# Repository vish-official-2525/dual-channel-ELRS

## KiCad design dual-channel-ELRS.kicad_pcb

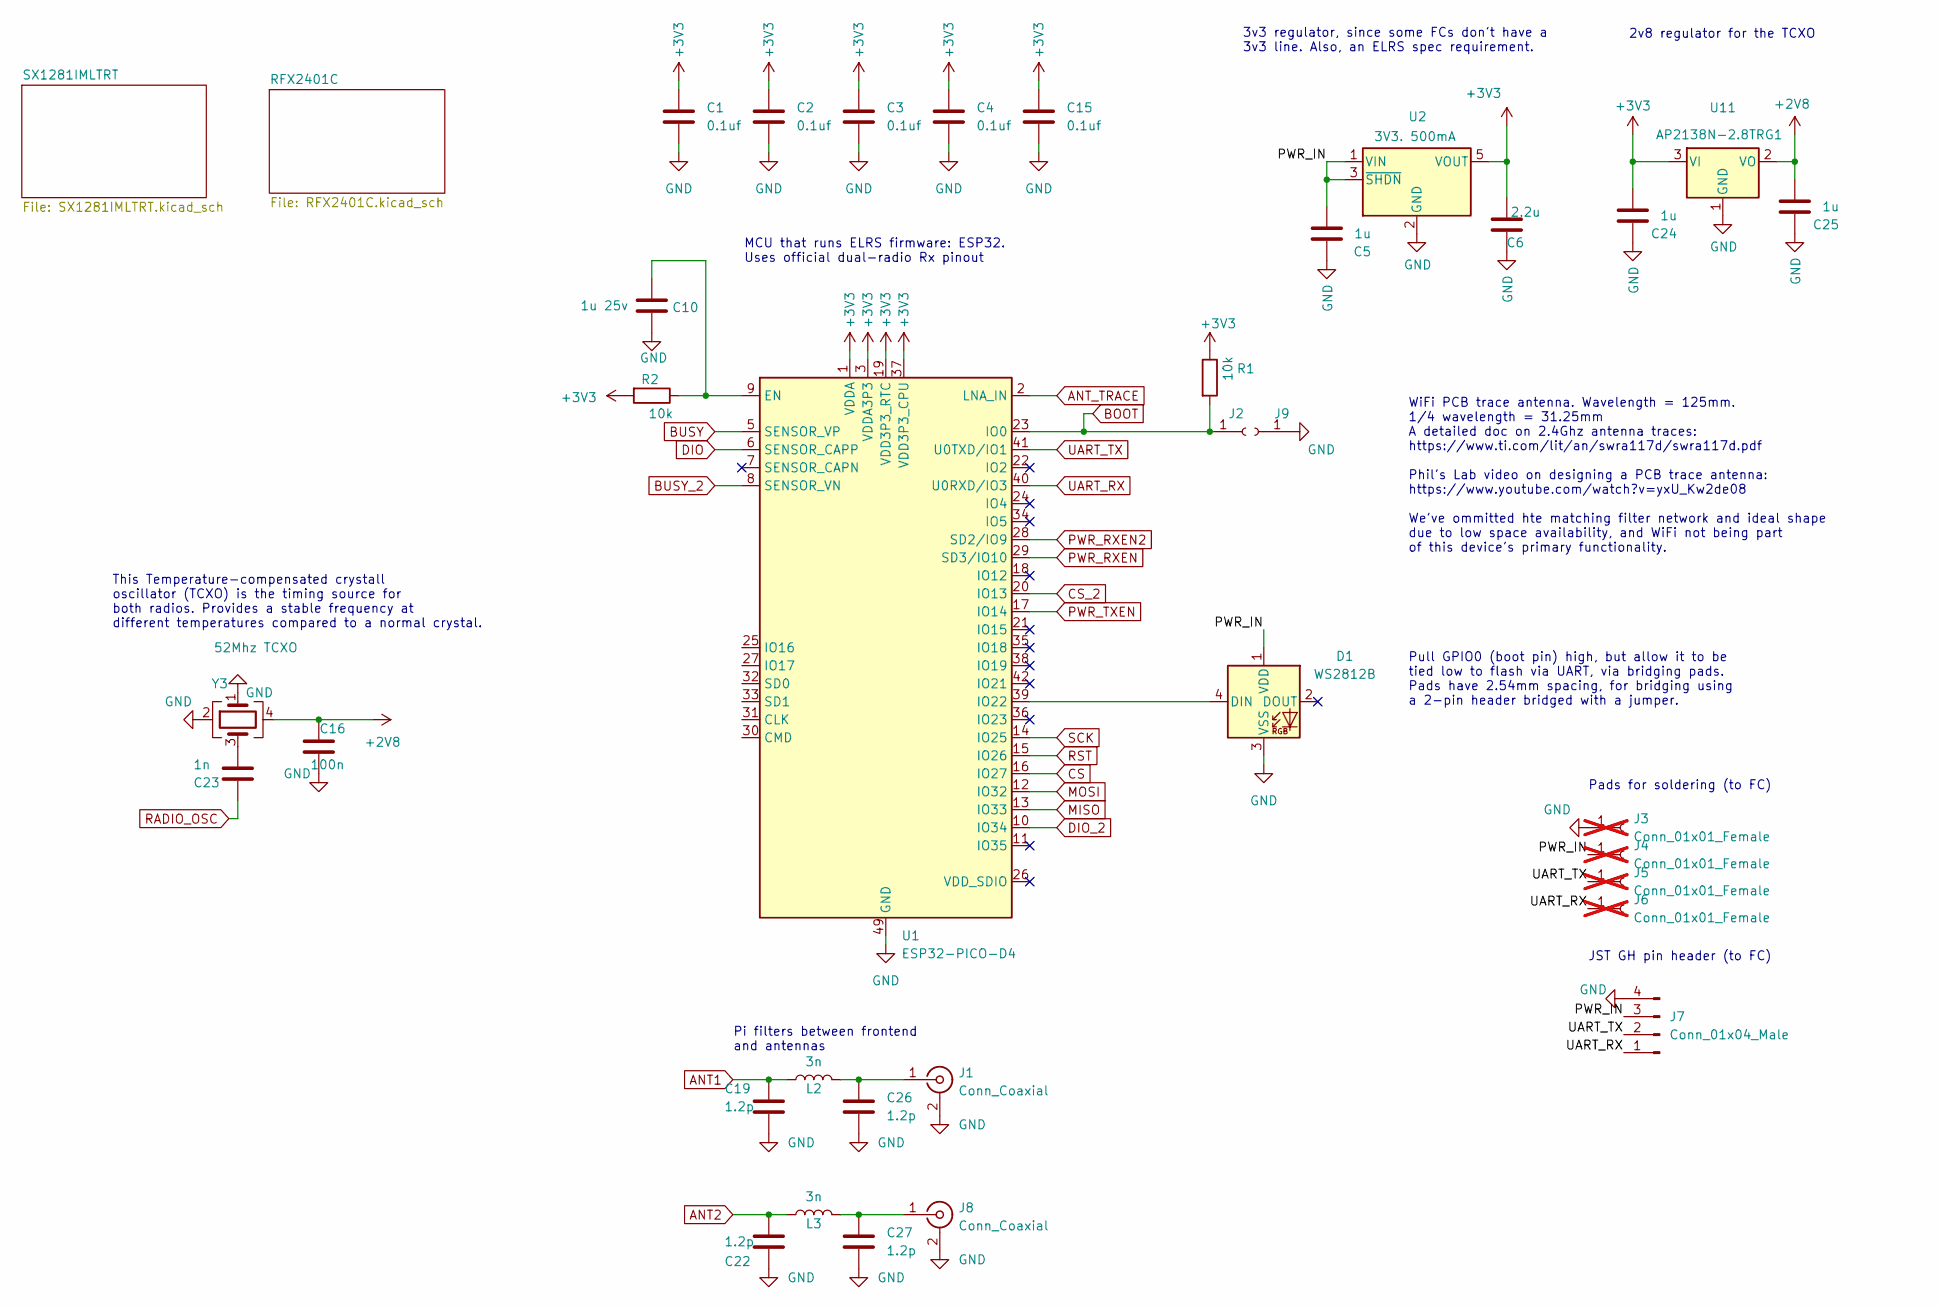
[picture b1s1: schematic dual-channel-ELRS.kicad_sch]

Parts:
C1, C2, C3, C4, C15: 0.1uf; C_0402_1005Metric
C5, C24, C25: 1u; C_0402_1005Metric; LCSC C52923
C6: 2.2u; C_0402_1005Metric; LCSC C12530
C10: 1u 25v; C_0402_1005Metric; LCSC C52923
C16: 100n; C_0402_1005Metric; LCSC C1525
C19, C22, C26, C27: 1.2p; C_0402_1005Metric; LCSC C327292
C23: 1n; C_0402_1005Metric; LCSC C1523
D1: WS2812B; LED_WS2812B_PLCC4_5.0x5.0mm_P3.2mm
J1, J8: Conn_Coaxial; U.FL_Hirose_U.FL-R-SMT-1_Vertical; Part Hirose U.FL-R-SMT-1(80); LCSC C88374
J2, J9: Conn_01x01_Female; TestPoint_Pad_1.0x1.0mm
J3, J4, J5, J6: Conn_01x01_Female; TestPoint_Pad_2.5x2.5mm; not fitted
J7: Conn_01x04_Male; JST_GH_SM04B-GHS-TB_1x04-1MP_P1.25mm_Horizontal; LCSC C189895
L2, L3: 3n; L_0402_1005Metric; LCSC C269824
R1, R2: 10k; R_0402_1005Metric; LCSC C25744
U1: ESP32-PICO-D4; QFN-48-1EP_7x7mm_P0.5mm_EP5.3x5.3mm
U2: 3V3. 500mA; TSOT-23-5; Part TPRT9013-33GB; LCSC C587158
U11: AP2138N-2.8TRG1; SOT-23; LCSC C176956
Y3: 52Mhz TCXO; Crystal_SMD_2016-4Pin_2.0x1.6mm; Digikey 2151-RTX-2016BD32-S-52.000-TR-NS1TR-ND

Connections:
BUSY_2: U1.8 (SENSOR_VN)
+2V8: C16.1, C25.2, U11.2 (VO), Y3.4
+3V3: C1.1, C2.1, C3.1, C4.1, C6.2, C15.1, C24.2, R1.1, R2.2, U1.1 (VDDA), U1.3 (VDDA3P3), U1.4 (VDDA3P3), U1.19 (VDD3P3_RTC), U1.37 (VDD3P3_CPU), U1.43 (VDDA), U1.46 (VDDA), U2.5 (VOUT), U11.3 (VI); also elsewhere on the board
/PWR_IN: C5.2, D1.1 (VDD), J4.1, J7.3, U2.1 (VIN), U2.3 (~SHDN)
ANT1: C19.1, L2.1; also elsewhere on the board
ANT2: C22.1, L3.1; also elsewhere on the board
ANT_TRACE: U1.2 (LNA_IN)
BOOT: J2.1, R1.2, U1.23 (IO0)
BUSY: U1.5 (SENSOR_VP); also elsewhere on the board
CS: U1.16 (IO27)
CS_2: U1.20 (IO13); also elsewhere on the board
DIO: U1.6 (SENSOR_CAPP); also elsewhere on the board
DIO_2: U1.10 (IO34)
GND: C1.2, C2.2, C3.2, C4.2, C5.1, C6.1, C10.2, C15.2, C16.2, C19.2, C22.2, C24.1, C25.1, C26.2, C27.2, D1.3 (VSS), J1.2 (Ext), J3.1, J7.4, J8.2 (Ext), J9.1, U1.49 (GND), U2.2 (GND), U11.1 (GND), Y3.1, Y3.2; also elsewhere on the board
MISO: U1.13 (IO33); also elsewhere on the board
MOSI: U1.12 (IO32); also elsewhere on the board
unnamed: C23.1, Y3.3
unnamed: D1.4 (DIN), U1.39 (IO22)
unnamed: C26.1, J1.1 (In), L2.2
unnamed: C27.1, J8.1 (In), L3.2
unnamed: C10.1, R2.1, U1.9 (EN)
PWR_RXEN: U1.29 (SD3/IO10); also elsewhere on the board
PWR_RXEN2: U1.28 (SD2/IO9); also elsewhere on the board
PWR_TXEN: U1.17 (IO14); also elsewhere on the board
RADIO_OSC: C23.2; also elsewhere on the board
RST: U1.15 (IO26); also elsewhere on the board
SCK: U1.14 (IO25); also elsewhere on the board
UART_RX: J6.1, J7.1, U1.40 (U0RXD/IO3)
UART_TX: J5.1, J7.2, U1.41 (U0TXD/IO1)

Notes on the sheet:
MCU that runs ELRS firmware: ESP32. Uses official dual-radio Rx pinout
2v8 regulator for the TCXO
Pi filters between frontend and antennas
Pads for soldering (to FC)
WiFi PCB trace antenna. Wavelength = 125mm. 1/4 wavelength = 31.25mm A detailed doc on 2.4Ghz antenna traces: https://www.ti.com/lit/an/swra117d/swra117d.pdf Phil's Lab video on designing a PCB trace antenna: https://www.youtube.com/watch?v=yxU_Kw2de08 We've ommitted hte matching filter network and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
This Temperature-compensated crystall oscillator (TCXO) is the timing source for both radios. Provides a stable frequency at different temperatures compared to a normal crystal.
3v3 regulator, since some FCs don't have a 3v3 line. Also, an ELRS spec requirement.
Pull GPIO0 (boot pin) high, but allow it to be tied low to flash via UART, via bridging pads. Pads have 2.54mm spacing, for bridging using a 2-pin header bridged with a jumper.
JST GH pin header (to FC)

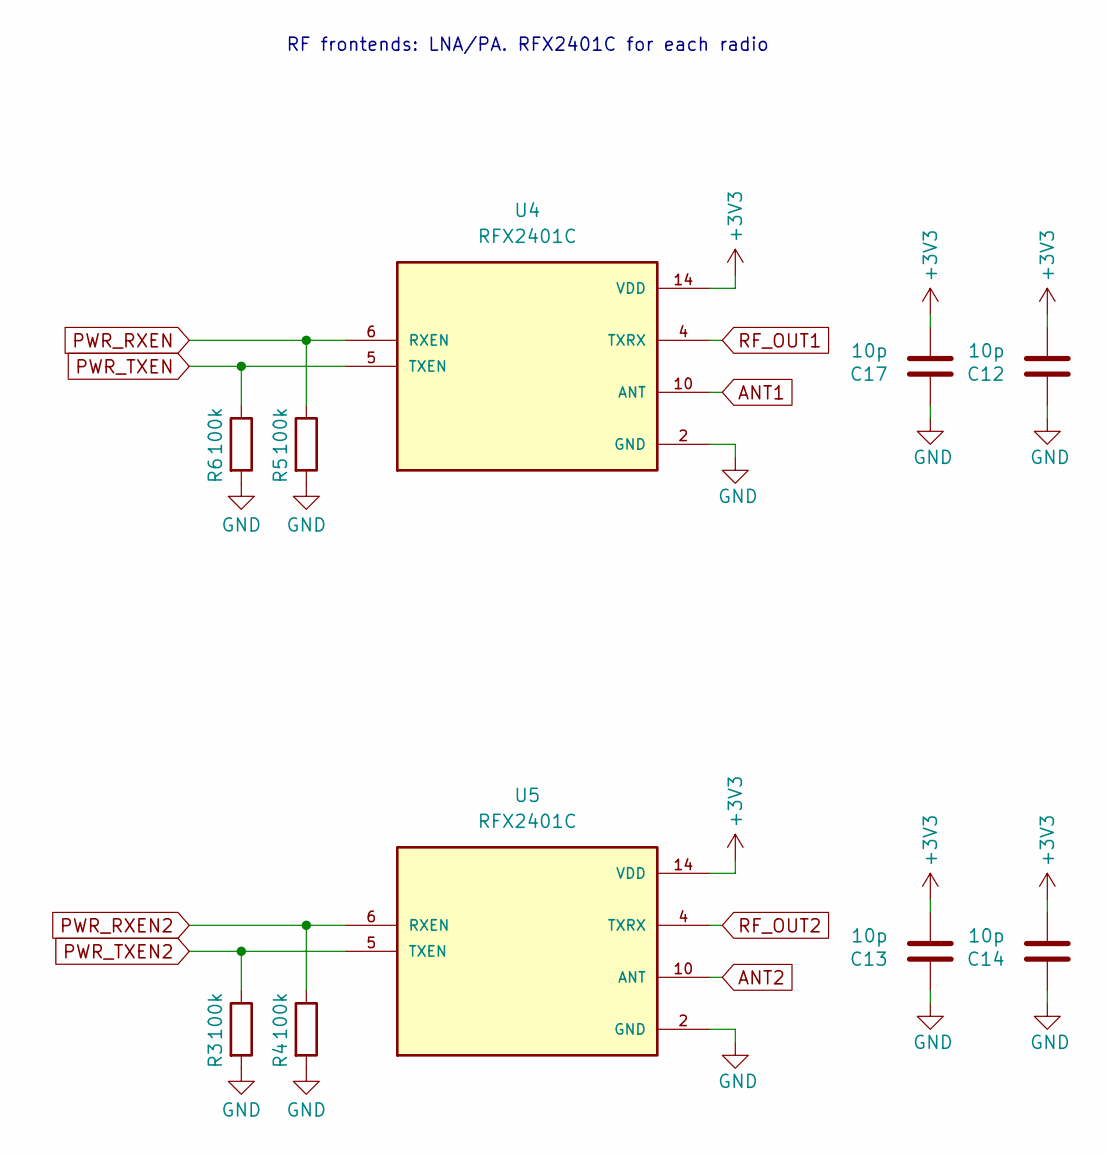
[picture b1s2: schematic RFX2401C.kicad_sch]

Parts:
C12, C13, C14, C17: 10p; C_0402_1005Metric; LCSC C32949
R3, R4, R5, R6: 100k; R_0402_1005Metric; LCSC C25741
U4, U5: RFX2401C; QFN50P300X300X60-17N; DigiKey_Part_Number 863-1828-1-ND

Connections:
+3V3: C12.2, C13.2, C14.2, C17.2, U4.14 (VDD), U4.16 (VDD), U5.14 (VDD), U5.16 (VDD); also elsewhere on the board
ANT1: U4.10 (ANT); also elsewhere on the board
ANT2: U5.10 (ANT); also elsewhere on the board
GND: C12.1, C13.1, C14.1, C17.1, R3.2, R4.2, R5.2, R6.2, U4.2 (GND), U4.3 (GND), U4.8 (GND), U4.9 (GND), U4.11 (GND), U4.17 (GND), U5.2 (GND), U5.3 (GND), U5.8 (GND), U5.9 (GND), U5.11 (GND), U5.17 (GND); also elsewhere on the board
PWR_RXEN: R5.1, U4.6 (RXEN); also elsewhere on the board
PWR_RXEN2: R4.1, U5.6 (RXEN); also elsewhere on the board
PWR_TXEN: R6.1, U4.5 (TXEN); also elsewhere on the board
PWR_TXEN2: R3.1, U5.5 (TXEN)
RF_OUT1: U4.4 (TXRX); also elsewhere on the board
RF_OUT2: U5.4 (TXRX); also elsewhere on the board

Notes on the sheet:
RF frontends: LNA/PA. RFX2401C for each radio

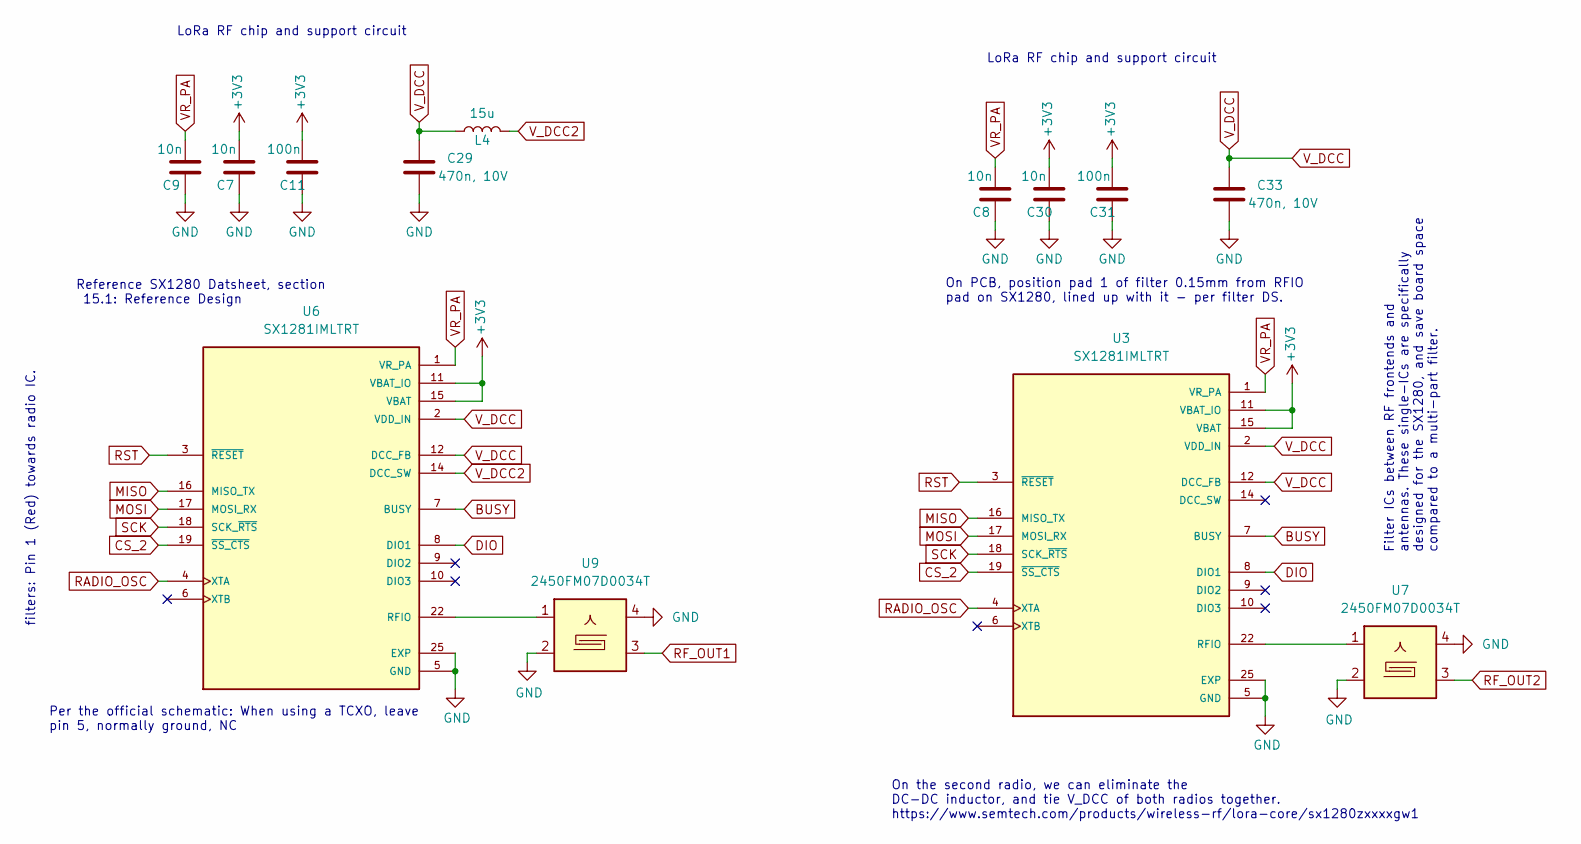
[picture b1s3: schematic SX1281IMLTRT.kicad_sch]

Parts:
C7, C8, C9, C30: 10n; C_0402_1005Metric; LCSC C15195
C11, C31: 100n; C_0402_1005Metric; LCSC C15195
C29, C33: 470n, 10V; C_0402_1005Metric; LCSC C47339
L4: 15u; L_0805_2012Metric; LCSC C486333
U3, U6: SX1281IMLTRT; XCVR_SX1281IMLTRT; PARTREV 3.3; DigiKey_Part_Number SX1281IMLTRTCT-ND
U7, U9: 2450FM07D0034T; FIL_2450FM07D0034T; Mouser 609-2450FM07D0034T

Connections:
+3V3: C7.1, C11.1, C30.1, C31.1, U3.11 (VBAT_IO), U3.15 (VBAT), U6.11 (VBAT_IO), U6.15 (VBAT); also elsewhere on the board
BUSY: U3.7 (BUSY), U6.7 (BUSY); also elsewhere on the board
CS_2: U3.19 (~SS_CTS), U6.19 (~SS_CTS); also elsewhere on the board
DIO: U3.8 (DIO1), U6.8 (DIO1); also elsewhere on the board
GND: C7.2, C8.2, C9.2, C11.2, C29.2, C30.2, C31.2, C33.2, U3.5 (GND), U3.13 (GND), U3.20 (GND), U3.21 (GND), U3.23 (GND), U3.24 (GND), U3.25 (EXP), U6.5 (GND), U6.13 (GND), U6.20 (GND), U6.21 (GND), U6.23 (GND), U6.24 (GND), U6.25 (EXP), U7.2, U7.4, U7.5, U9.2, U9.4, U9.5; also elsewhere on the board
MISO: U3.16 (MISO_TX), U6.16 (MISO_TX); also elsewhere on the board
MOSI: U3.17 (MOSI_RX), U6.17 (MOSI_RX); also elsewhere on the board
unnamed: U3.22 (RFIO), U7.1
unnamed: U6.22 (RFIO), U9.1
RADIO_OSC: U3.4 (XTA), U6.4 (XTA); also elsewhere on the board
RF_OUT1: U9.3; also elsewhere on the board
RF_OUT2: U7.3; also elsewhere on the board
RST: U3.3 (~RESET), U6.3 (~RESET); also elsewhere on the board
SCK: U3.18 (SCK_~RTS), U6.18 (SCK_~RTS); also elsewhere on the board
VR_PA: C8.1, C9.1, U3.1 (VR_PA), U6.1 (VR_PA)
V_DCC: C29.1, C33.1, L4.1, U3.2 (VDD_IN), U3.12 (DCC_FB), U6.2 (VDD_IN), U6.12 (DCC_FB)
V_DCC2: L4.2, U6.14 (DCC_SW)

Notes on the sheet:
LoRa RF chip and support circuit
On the second radio, we can eliminate the DC-DC inductor, and tie V_DCC of both radios together. https://www.semtech.com/products/wireless-rf/lora-core/sx1280zxxxxgw1
filters: Pin 1 (Red) towards radio IC.
Reference SX1280 Datsheet, section 15.1: Reference Design
Per the official schematic: When using a TCXO, leave pin 5, normally ground, NC
Filter ICs between RF frontends and antennas. These single-ICs are specifically designed for the SX1280, and save board space compared to a multi-part filter.
On PCB, position pad 1 of filter 0.15mm from RFIO pad on SX1280, lined up with it - per filter DS.

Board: 4 copper layers, 57 parts (26 on the bottom side), 33 nets, no tracks yet.

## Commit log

2026-02-16 dual-channel-ELRS
2026-02-16 model
